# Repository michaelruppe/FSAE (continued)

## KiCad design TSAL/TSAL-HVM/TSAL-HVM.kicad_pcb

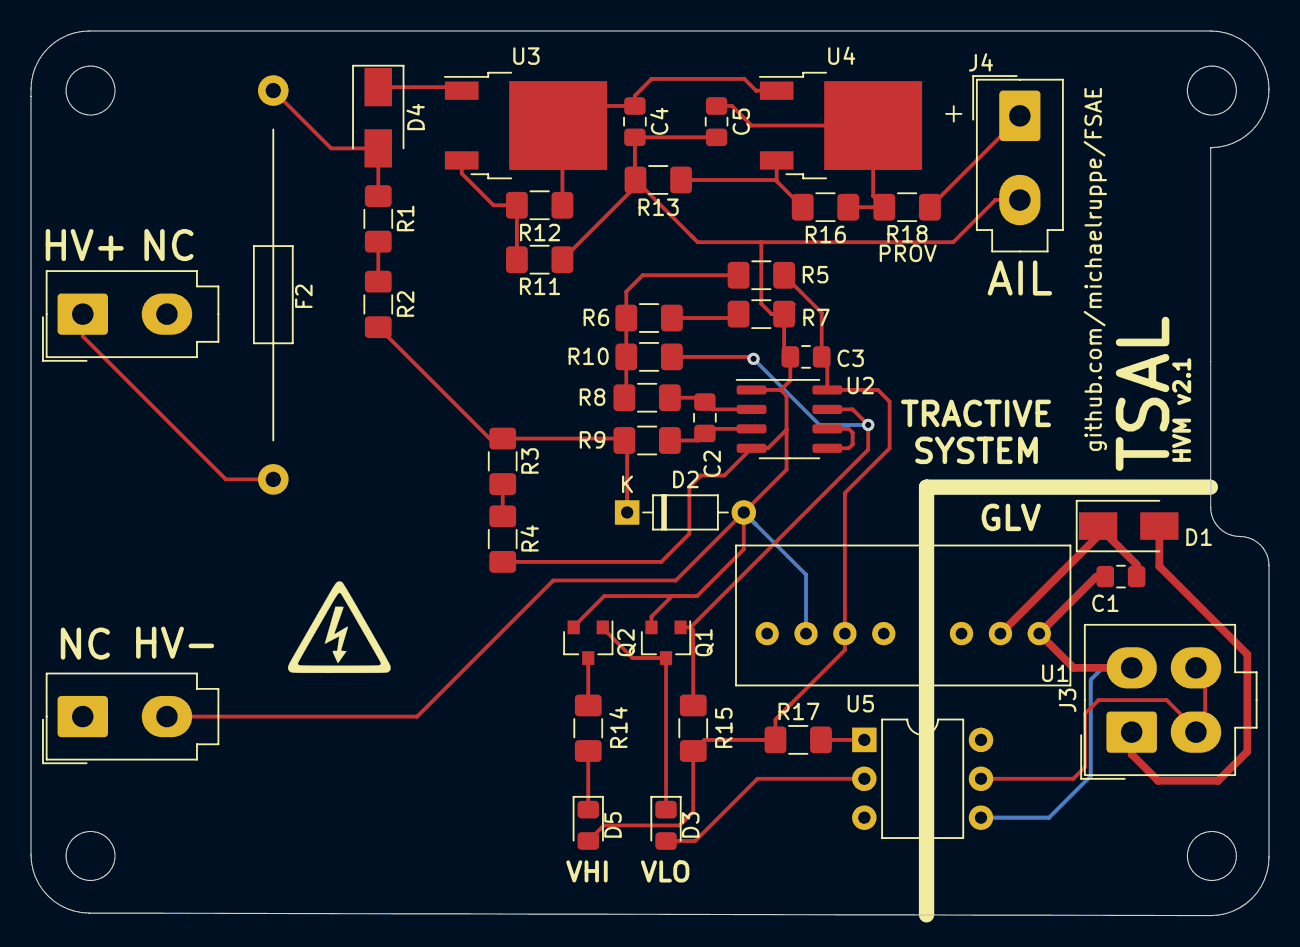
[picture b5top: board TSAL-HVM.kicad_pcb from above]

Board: 2 copper layers, 80.9 x 57.8 mm, 40 parts (0 on the bottom side), 28 nets.

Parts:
C1, C4, C5: 1u; C_0805_2012Metric_Pad1.15x1.40mm_HandSolder
C2: 10n; C_0805_2012Metric_Pad1.15x1.40mm_HandSolder
C3: 100n; C_0805_2012Metric_Pad1.15x1.40mm_HandSolder
D1, D4: D; D_SMA
D2: 12V; D_DO-35_SOD27_P7.62mm_Horizontal
D3: VLO; LED_0805_2012Metric_Pad1.15x1.40mm_HandSolder
D5: VHI; LED_0805_2012Metric_Pad1.15x1.40mm_HandSolder
F2: Fuse_Small; BELFUSE-5HF
J1: HV+; Molex_Mini-Fit_Jr_5566-02A_2x01_P4.20mm_Vertical
J2: HV-; Molex_Mini-Fit_Jr_5566-02A_2x01_P4.20mm_Vertical
J3: Conn_01x04_Male; Molex-Mini-Fit-Jr-4-pin-P4.2mm-RowP4.2mm
J4: AIL; Molex_Mini-Fit_Jr_5566-02A_2x01_P4.20mm_Vertical
Q1, Q2: 2N7002; SOT-23
R1, R2: 499k; R_1206_3216Metric_Pad1.42x1.75mm_HandSolder
R3: 49k9; R_1206_3216Metric_Pad1.42x1.75mm_HandSolder
R4, R17: 2k2; R_1206_3216Metric_Pad1.42x1.75mm_HandSolder
R5: 75k; R_1206_3216Metric_Pad1.42x1.75mm_HandSolder
R6: 24k; R_1206_3216Metric_Pad1.42x1.75mm_HandSolder
R7: 900; R_1206_3216Metric_Pad1.42x1.75mm_HandSolder
R8, R9: 100; R_1206_3216Metric_Pad1.42x1.75mm_HandSolder
R10: 1M; R_1206_3216Metric_Pad1.42x1.75mm_HandSolder
R11: 202k; R_1206_3216Metric_Pad1.42x1.75mm_HandSolder
R12, R16: 6k04; R_1206_3216Metric_Pad1.42x1.75mm_HandSolder
R13: 47k; R_1206_3216Metric_Pad1.42x1.75mm_HandSolder
R14: 3k3; R_1206_3216Metric_Pad1.42x1.75mm_HandSolder
R15: 10k; R_1206_3216Metric_Pad1.42x1.75mm_HandSolder
R18: PROV; R_1206_3216Metric_Pad1.42x1.75mm_HandSolder
U1: SPAN02A-12; SPAN02
U2: LM311; SOIC-8_3.9x4.9mm_P1.27mm
U3, U4: LR8K4-G; TO-252-2
U5: MOC8021; DIP-6_W7.62mm

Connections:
+12V: C3.1, D5.2, R5.2, R15.1, R17.1, U1.6, U2.8
/+HV: F2.1, J1.1
/VHI: J3.3, J3.4, U5.5
/Vin: D2.1, R2.2, R3.1, R9.2
/Vref: R5.1, R6.2, R8.2, R10.1
GND: C3.2, C4.2, C5.2, D2.2, J2.2, J4.2, Q1.2, Q2.2, R4.2, R7.1, R11.2, R13.2, U1.7, U2.1, U2.4
GNDPWR: C1.1, J3.2, U1.1, U5.4
unnamed: C1.2, D1.1, U1.2
unnamed: C2.1, R8.1, U2.2
unnamed: C2.2, R9.1, U2.3
unnamed: C4.1, R12.1, U3.2, U4.1
unnamed: C5.1, R16.1, R18.1, U4.2
unnamed: D1.2, J3.1
unnamed: D3.1, Q1.3, Q2.1
unnamed: D3.2, U5.2
unnamed: D4.1, U3.1
unnamed: D4.2, F2.2, R1.1
unnamed: D5.1, R14.1
unnamed: J4.1, R18.2
unnamed: Q1.1, R10.2, R15.2, U2.7
unnamed: Q2.3, R14.2
unnamed: R1.2, R2.1
unnamed: R3.2, R4.1
unnamed: R6.1, R7.2
unnamed: R11.1, R12.2, U3.3
unnamed: R13.1, R16.2, U4.3
unnamed: R17.2, U5.1
unnamed: U2.5, U2.6

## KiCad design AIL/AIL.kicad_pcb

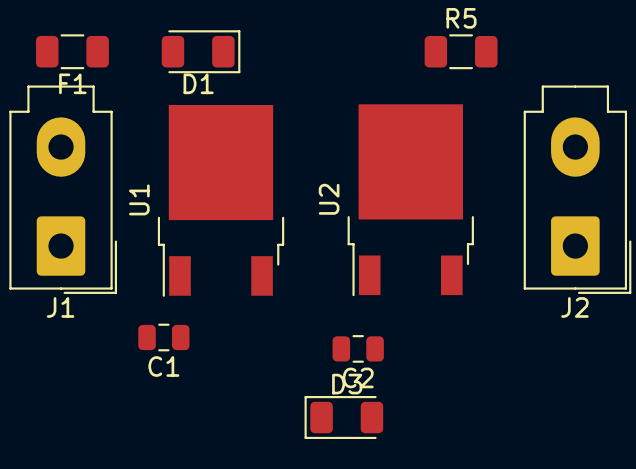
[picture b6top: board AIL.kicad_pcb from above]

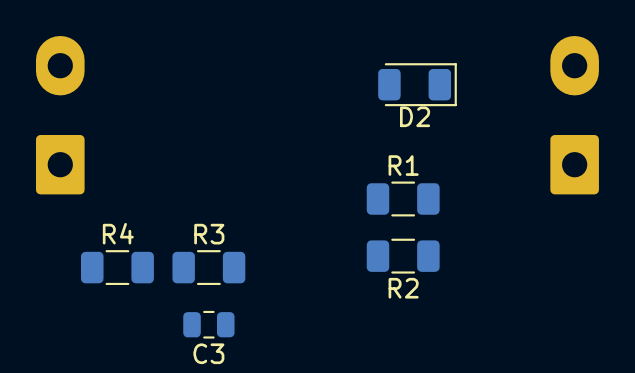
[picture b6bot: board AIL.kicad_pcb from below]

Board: 2 copper layers, 16 parts (6 on the bottom side), 9 nets, no tracks yet.

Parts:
C1: 10n; C_0805_2012Metric
C2, C3: 1uF; C_0805_2012Metric
D1, D2, D3: D; D_1206_3216Metric
F1: Polyfuse; Fuse_1206_3216Metric
J1: HV-IN; Molex_Mini-Fit_Jr_5566-02A_2x01_P4.20mm_Vertical
J2: AIL-OUT; Molex_Mini-Fit_Jr_5566-02A_2x01_P4.20mm_Vertical
R1, R3: 6k04; R_1206_3216Metric
R2: 202k; R_1206_3216Metric
R4: 47k; R_1206_3216Metric
R5: PROV; R_1206_3216Metric
U1, U2: LR8K4-G; TO-252-2

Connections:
unnamed: C1.1, D1.1, D2.1, U1.1
unnamed: C1.2, C2.2, C3.2, J1.2, J2.1, R2.1, R4.1
unnamed: C2.1, D2.2, D3.1, R1.2, U1.2, U2.1
unnamed: C3.1, D3.2, R3.2, R5.1, U2.2
unnamed: D1.2, F1.1
unnamed: F1.2, J1.1
unnamed: J2.2, R5.2
unnamed: R1.1, R2.2, U1.3
unnamed: R3.1, R4.2, U2.3

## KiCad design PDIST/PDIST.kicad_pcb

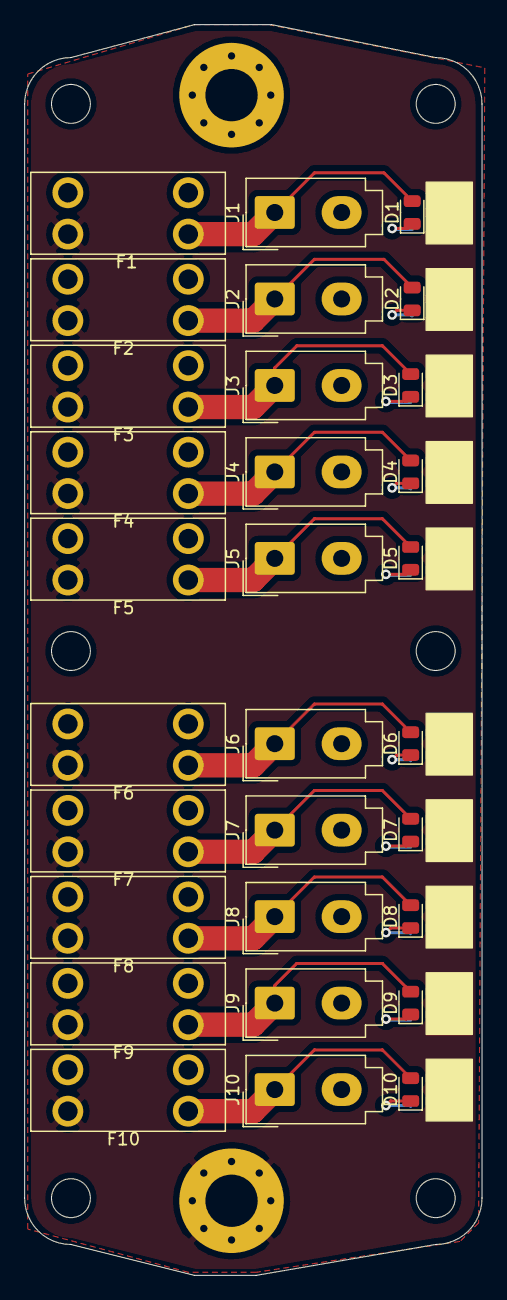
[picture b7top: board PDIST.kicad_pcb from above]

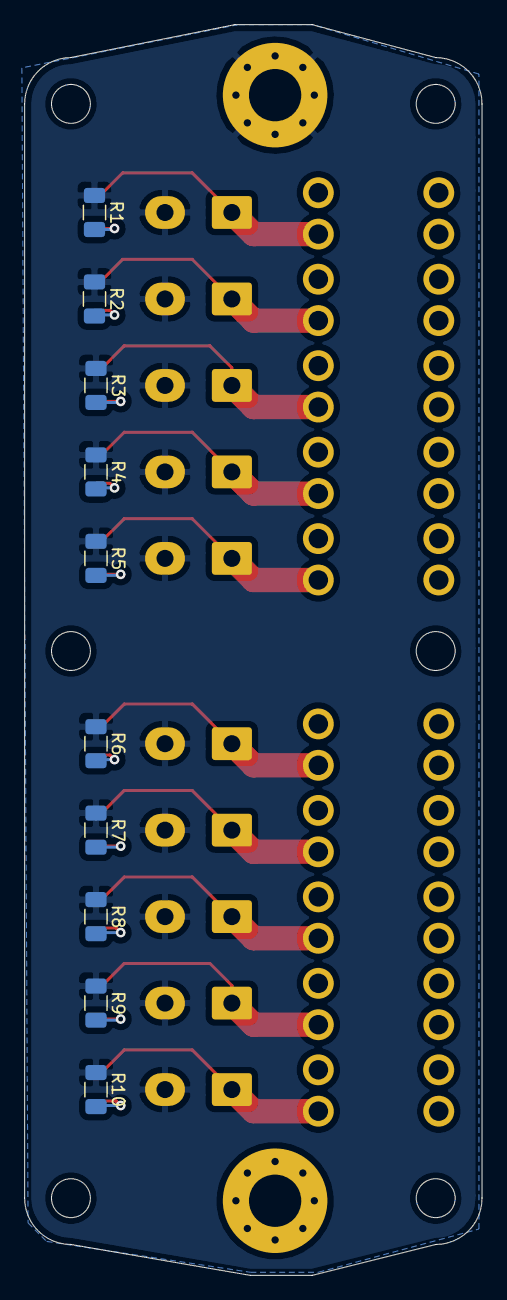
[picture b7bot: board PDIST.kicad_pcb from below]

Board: 2 copper layers, 37.6 x 102.9 mm, 42 parts (10 on the bottom side), 22 nets.

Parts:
D1, D2, D3, D4, D5, D6, D7, D8, D9, D10: LED; LED_0805_2012Metric
F1, F2, F3, F4, F5, F6, F7, F8, F9, F10: Fuse; Fuse-Mini_Blade-3568
H1, H2: MountingHole_Pad; MountingHole_4.3mm_M4_Pad_Via
J1, J2, J3, J4, J5, J6, J7, J8, J9, J10: Conn_01x02_Male; Molex_Mini-Fit_Jr_5566-02A_2x01_P4.20mm_Vertical
R1, R2, R3, R4, R5, R6, R7, R8, R9, R10: R; R_1206_3216Metric

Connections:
GND: H2.1, J1.2, J2.2, J3.2, J4.2, J5.2, J6.2, J7.2, J8.2, J9.2, J10.2, R1.1, R2.1, R3.1, R4.1, R5.1, R6.1, R7.1, R8.1, R9.1, R10.1
unnamed: D1.1, R1.2
unnamed: D1.2, F1.1, J1.1
unnamed: D2.1, R2.2
unnamed: D2.2, F2.1, J2.1
unnamed: D3.1, R3.2
unnamed: D3.2, F3.1, J3.1
unnamed: D4.1, R4.2
unnamed: D4.2, F4.1, J4.1
unnamed: D5.1, R5.2
unnamed: D5.2, F5.1, J5.1
unnamed: D6.1, R6.2
unnamed: D6.2, F6.1, J6.1
unnamed: D7.1, R7.2
unnamed: D7.2, F7.1, J7.1
unnamed: D8.1, R8.2
unnamed: D8.2, F8.1, J8.1
unnamed: D9.1, R9.2
unnamed: D9.2, F9.1, J9.1
unnamed: D10.1, R10.2
unnamed: D10.2, F10.1, J10.1
unnamed: F1.2, F2.2, F3.2, F4.2, F5.2, F6.2, F7.2, F8.2, F9.2, F10.2, H1.1

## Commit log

2019-08-14 Update TSAL-HVM to v1.1
    Move indicator LED text to silk layer
    Fix wayward trace HV- to GND
2019-08-14 Add Hard Fault Latch board
2019-08-15 Update HFL - include indicator lamp outputs (low-side)
2019-08-15 Add render and schematic images
2019-08-15 Add README
2019-08-15 Update README - failure modes and recommendations
2019-08-20 Finalise HFL v1
2019-08-27 commit before revising some pcbs
2019-08-28 Update HFL
2019-08-28 update j2 pinout to match CCU board
2019-08-31 Update TSAL-HVMv1.1 with lessons learned from assembling v1
2019-09-01 update routed slot
2019-09-01 PCB: Remove routed slot. Update render
2019-09-01 Update schematic labels and README
2019-09-01 update render to high-quality. ray-traced
2019-09-01 update render background to white
2019-09-03 Aesthetic upgrades to schematic, render
2019-09-03 Update README - HVM component references in description
2019-09-04 add Accumulator Indicator - preliminary design
2019-09-21 Add AIL schematic. Add TSAL-DRV pinout diagram
2019-09-21 update readme, include images
2019-09-21 correct pinout
2019-09-22 Update TSAL to v2. Add AIL
2019-09-23 Update TSAL with connector 3D models
2019-10-01 update tsal-hvm render name README
2019-10-01 Update HFL schematic to use logic chips instead of relay latching-logic
2019-10-02 Update HFL with additional commissioning features
2019-10-02 Update HFL PCB - preliminary component placement
2019-10-02 Update HFL PCB Faults and statuses now independent. Working on part placement
2019-10-03 Update HFL - tentatively complete v2 routing still need to select parts
2019-10-09 Cosmetic upgrades to HFL v2
    also scattered some GND-GND vias
2019-10-09 update schematic minor
2019-10-09 Update to v2.1
    cosmetic changes to silkscreen. Remove power input fuse
2019-10-09 Add MOBO: Sketch-out motherboard idea
2019-10-10 Update HFL - pcb silk
2019-10-10 Update TSAL-DRV to v2 schematic and select parts. Need route board
2019-10-29 Add CELL-MOUNT FR4 design
    For mounting cells in accumulator
2019-10-29 add dimensional drawing for reference
2019-12-11 Update TSAL versioning, renders and schematic prints
2020-01-22 Lock down before branch for projects
2020-01-22 remove MOBO
2020-01-24 add Precharge
2020-01-27 create precharge and prelim simulations
2020-01-29 Update precharge schematic
2020-01-29 Precharge: update schematic to uController preliminary
2020-02-11 Add TSALv3
2020-03-03 cleanup TSALv3 models
2020-03-03 Update precharge design. Begin PCB layup
2020-03-03 add resistor calcs
2020-03-03 add mini-fit-jr STEP files
2020-03-11 Documentation, aesthetic upgrades
2020-03-11 Update precharge design
2020-03-11 update render and readme
2020-03-16 cleanup junk
2020-03-16 update precharge schematic + pcb
2020-03-17 Include .step files used for PCB renders
2020-03-17 add SPAN02.step
2020-03-17 :hammer: Precharge:arrange components
2020-03-17 🛀 cleanup unsued .stp files
2020-03-17 ✏️ add REAMDE
2020-03-17 ✏️ update README
2020-03-18 :straight_ruler: spec frequency optocouplers properly
2020-03-18 Add datasheet to LM331
2020-03-18 :hammer: fix LM331 circuits (Voltage-frequency)
2020-03-18 :hammer: position components, add CAD models
2020-03-18 :hourglass_flowing_sand: hand-route crucial sections
2020-03-19 Update License with github profile information
2020-03-19 :pencil: Update Readme
2020-03-19 :pencil: simulate optocoupler
2020-03-19 :pencil: Add connector cad files and associate with footprints.
2020-03-19 :pencil2: manual route the critical paths
2020-03-19 :hammer: complete routing
2020-03-19 :hammer: PCB artwork
2020-03-21 :pencil: Add title-block info
2020-03-21 :pencil: add precharge_code/ and begin coding project
2020-03-21 🔩 Connect CAN transceiver S->GND
2020-03-21 :pencil: correctly initialise GPIO inputs with pullups
2020-03-21 :pencil: wireframe state functions
2020-03-22 :hammer: Add PCB artwork for status LEDs
2020-03-22 :pencil: tidy-up pcb artwork
2020-03-24 :pencil2: Wireframe CANboy
2020-03-25 :pencil2: create libraries and update schematic
2020-03-25 build libraries for IMU
2020-04-19 :star: add V-F Experiment
2020-04-19 :star: got VF-response
2020-04-19 :star: can measure high voltages
2020-04-19 :star: forgot to add these to last commit
2020-04-19 :pencil: ignore Microsoft Excel temp files
2020-04-19 :sunflower: Add precharge render
2020-04-20 Conduct precharge experiment
2020-04-20 :star: copy changes from log-voltage to precharge_code
2020-04-20 :hammer: add moving average filter and experiment
2020-04-20 :bathtub: cleanup - rename projects and update readme
2020-04-20 :page_with_curl: Rename experiments
2020-04-20 :pencil: add recommendation
2020-04-20 :hammer: add major project code. Begin state machine
2020-04-20 :pencil: Add usage example
2020-04-20 :star: Working state machine
    Ready for commissioning and finding all the bugs :D
2020-04-20 :nut_and_bolt: Move string literals to flash memory
2020-04-20 :sweat_smile: REALLY working state machine
2020-04-20 :pencil2: improve output messaging
2020-04-20 :pencil2: improve output messages
2020-04-20 :pencil: update feature list
2020-04-20 :pencil: improve function description for getFrequency()
2020-04-20 :pencil: improve commenting
2020-04-20 :hammer: Add StatusLed class
2020-04-21 :hammer: Improve StatusLed class
    add manual on, off functions, better constructor and update functions
2020-04-21 improve update(on,off) function
    don't update NOW - if user called function repeatedly it will cause
    erratic behaviour. better to wait for the once-per-loop update()
    function
2020-04-21 :hammer: add status LED behaviour, precharge progress print()
2020-04-21 :bathtub: fix string format for precharge progress
2020-04-21 :pencil2: update error status light behaviour
2020-04-21 :hammer: add reset functionality
2020-04-21 :hammer: reset moving averages prevents errors, better formatted strings
2020-04-21 :hammer: only reset moving average when ENTERING the state.
    Also, add a sample rate to the shutdown circuit
2020-04-21 :pencil2: rename STATE_RUNNING to STATE_ONLINE
2020-04-21 :arrow_forward: Move Experiments.xlsx
2020-04-21 :pencil: documentation + diagrams
2020-04-21 :pencil: update figure dimensions
2020-04-21 :pencil: Figure labels
2020-04-21 :pencil: fix list indent
2020-04-21 :pencil2: Documentation: comment header
2020-04-22 :pencil: Add commissioning notes
2020-04-22 :pencil: Update commissioning notes
2020-04-22 :pencil: update readme - experimental results
2020-04-22 :pencil2: typo
2020-04-22 :hammer: update component values to prototype as-built
2020-04-22 :hammer: update board routing to reflect bodges made in prototyping
2020-04-22 :pencil: document precharge resistor selection
2020-04-22 :hammer: add schematic pdf
2020-04-22 :hammer: add table of contents
2020-04-22 update with plot
2020-04-22 :hammer: fix table of contents
2020-04-22 :arrow_right: move schematic and update readme
2020-04-22 :hammer: add pinout pdf
2020-04-22 :hammer: add recommendation
2020-04-22 :star: improve How to modify this design section
2020-04-29 :pencil: refactor SDC voltage. comments, notes
2020-04-29 :pencil2: update readmes
2020-04-29 :pencil: include/move datasheets and figures
2020-04-29 :hammer: update PDOC component value - reference voltage
2020-04-29 :pencil2: update readme - PDOC commissioning
2020-04-29 :star: update schematic pdf
2020-04-30 :update TSALv3: schematic (cosmetic)
    remove note on D2 - this should ALWAYS be populated
    increment version to v3.1 - no physical changes, only the important removal of note on D2
2020-05-18 :star: update HFLv2.1
2020-05-18 :hammer: include StatusLEDsOff() function
2020-05-29 :hammer: Fix error with 555 timer
2024-05-11 Update README.md
    Fix typo
2026-04-02 Update README.md with shutdowncircuit.com link
